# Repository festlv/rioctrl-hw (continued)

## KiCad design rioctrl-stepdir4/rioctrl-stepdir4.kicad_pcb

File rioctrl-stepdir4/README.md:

# rioctrl-stepdir4

This module provides 4 axis of step/dir/enable signals.
* Step/dir signals are differential 5V.
* Enable signal is at the same voltage as controller's DC input.

The connectors are RJ45 (intended use is either with motor-drive specific breakout board or a generic screw-terminal type breakout board).

RJ45 green LED is wired to enable signal.

## Pinout (when using breakouts/rioctrl-rj45-breakout):

| Pin | Signal |
|-----|--------|
| 1   | Step + |
| 2   | Step - |
| 3   | Dir -  |
| 4   | Enable |
| 5   | GND    |
| 6   | Dir -  |
| 7   | GND    |
| 8   | GND    |

# Changelog

## v1.1
* Fixed slot's pin-header position (was offset by 4 mm)
* Rename silkscreen labels from axis 1..4 to join 0..3 to match riocore/LinuxCNC convention
 
## v1.0
Initial released version.

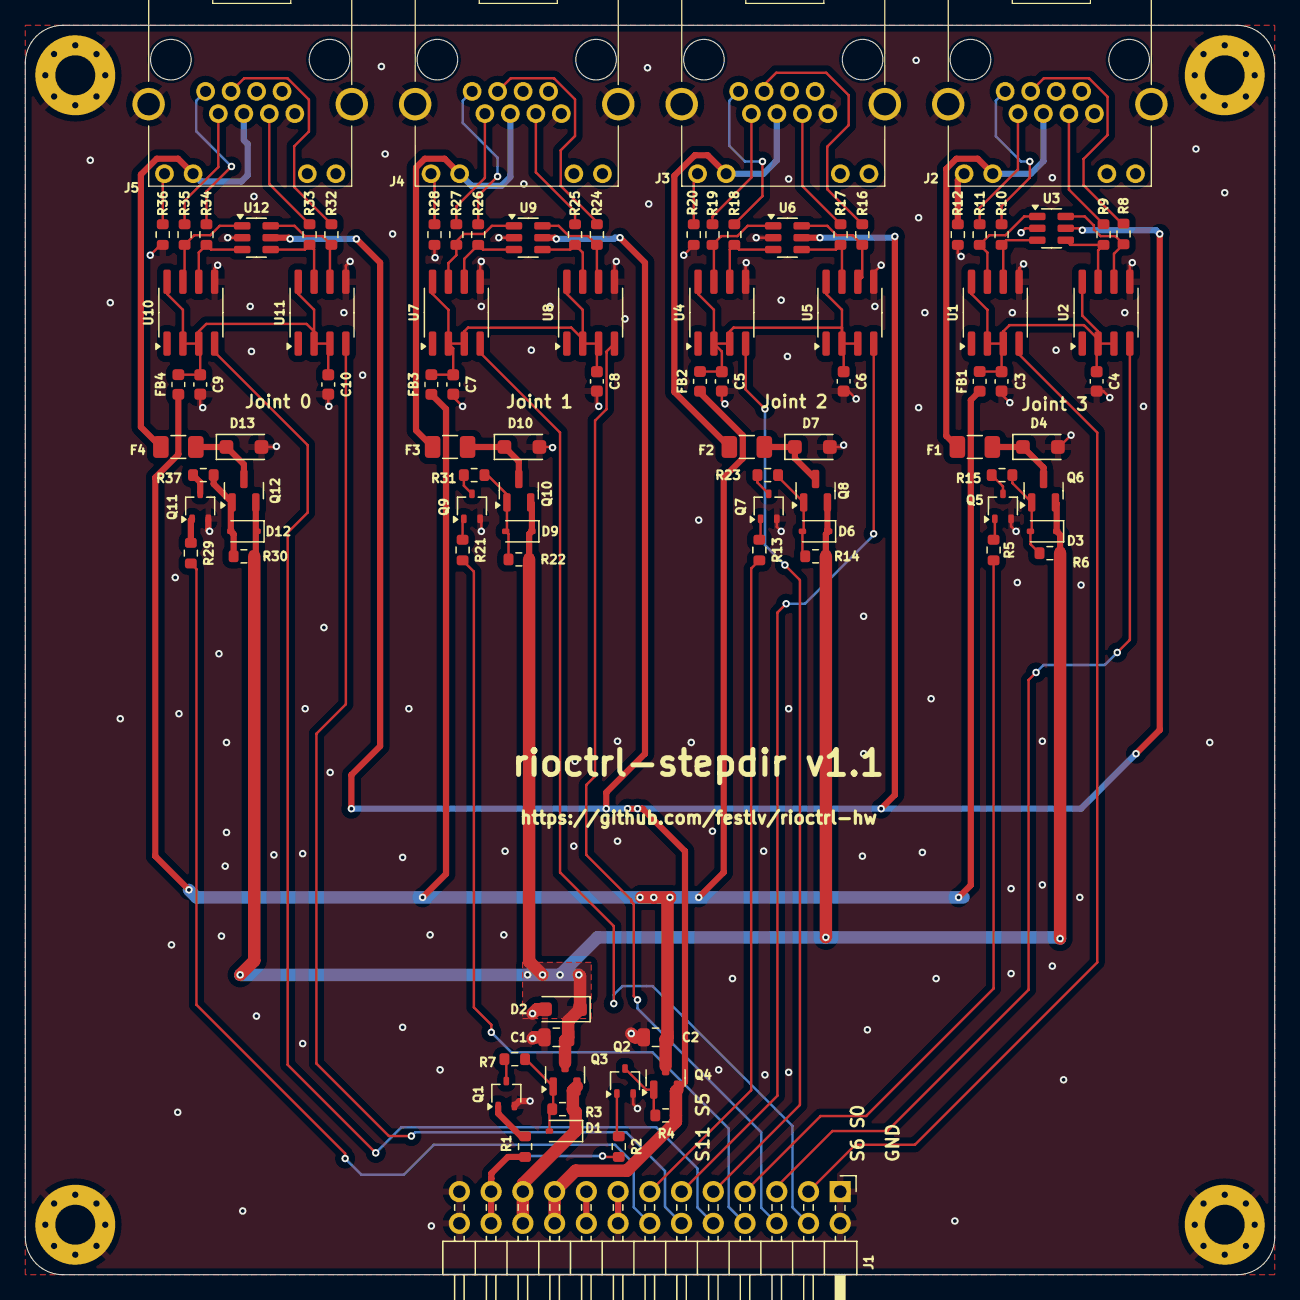
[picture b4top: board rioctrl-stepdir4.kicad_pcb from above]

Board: 2 copper layers, 100.0 x 100.0 mm, 98 parts (0 on the bottom side), 84 nets.

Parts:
C1, C2: 10uF; C_0805_2012Metric
C3, C4, C5, C6, C7, C8, C9, C10: 0.1uF; C_0603_1608Metric
D1, D3, D6, D9, D12: BZT52C10S; D_SOD-323
D2, D4, D7, D10, D13: SMF24A; D_SOD-123F
F1, F2, F3, F4: BSMD1206-100-24V; Fuse_1206_3216Metric
FB1, FB2, FB3, FB4: FB_100R_3A; L_0603_1608Metric
H1, H2, H3, H4: MH_3.2mm; MountingHole_3.2mm_M3_Pad_Via
J1: Conn_02x13_Odd_Even; PinHeader_2x13_P2.54mm_Horizontal
J2, J3, J4, J5: RJ45_LED_Shielded; R-RJ45R08P-C000
Q1, Q2, Q5, Q7, Q9, Q11: BSS138W; SOT-323_SC-70
Q3, Q4, Q6, Q8, Q10, Q12: AO3401A; SOT-23
R1, R2, R3, R4, R5, R6, R7, R12, R13, R14, R15, R20, R21, R22, R23, R28, R29, R30, R31, R36, R37: 10K; R_0603_1608Metric
R8, R9, R10, R11, R16, R17, R18, R19, R24, R25, R26, R27, R32, R33, R34, R35: 100R; R_0603_1608Metric
U1, U2, U4, U5, U7, U8, U10, U11: CS48505S; SOIC-8_3.9x4.9mm_P1.27mm
U3, U6, U9, U12: USBLC6-4SC6; SOT-23-6

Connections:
+3V3: J1.17, J1.18
+5V: J1.19, J1.20, Q4.2 (S), R4.1, U3.5 (VBUS), U6.5 (VBUS), U9.5 (VBUS), U12.5 (VBUS)
+5V_EN: C2.1, FB1.1, FB2.1, FB3.1, FB4.1, Q4.3 (D)
+24V: D1.1 (K), J1.21, J1.22, Q3.2 (S), R3.1
+24V_EN: C1.1, D2.1 (A1), D3.1 (K), D6.1 (K), D9.1 (K), D12.1 (K), Q3.3 (D), Q6.2 (S), Q8.2 (S), Q10.2 (S), Q12.2 (S), R6.1, R14.1, R22.1, R30.1
/Slot input/S0: J1.3, U1.4 (DI)
/Slot input/S1: J1.5, U2.4 (DI)
/Slot input/S2: J1.7, R5.2
/Slot input/S3: J1.9, U4.4 (DI)
/Slot input/S4: J1.11, U5.4 (DI)
/Slot input/S5: J1.13, R13.2
/Slot input/S6: J1.4, U7.4 (DI)
/Slot input/S7: J1.6, U8.4 (DI)
/Slot input/S8: J1.8, R21.2
/Slot input/S9: J1.10, U10.4 (DI)
/Slot input/S10: J1.12, U11.4 (DI)
/Slot input/S11: J1.14, R29.2
/Slot input/SlotEN: J1.23, J1.24, R1.2, R2.2
/Step dir output 1/DIR_OUT_N: R33.1, U11.7 (B), U12.4 (I/O3)
/Step dir output 1/DIR_OUT_P: R32.1, U11.6 (A), U12.6 (I/O4)
/Step dir output 1/DIR_OUT_P_N: J5.6, R33.2
/Step dir output 1/DIR_OUT_P_P: J5.3, R32.2
/Step dir output 1/EN_OUT: F4.2, J5.4, J5.10
/Step dir output 1/STEP_OUT_N: R35.1, U10.7 (B), U12.1 (I/O1)
/Step dir output 1/STEP_OUT_P: R34.1, U10.6 (A), U12.3 (I/O2)
/Step dir output 1/STEP_OUT_P_N: J5.2, R35.2
/Step dir output 1/STEP_OUT_P_P: J5.1, R34.2
/Step dir output 2/DIR_OUT_N: R25.1, U8.7 (B), U9.4 (I/O3)
/Step dir output 2/DIR_OUT_P: R24.1, U8.6 (A), U9.6 (I/O4)
/Step dir output 2/DIR_OUT_P_N: J4.6, R25.2
/Step dir output 2/DIR_OUT_P_P: J4.3, R24.2
/Step dir output 2/EN_OUT: F3.2, J4.4, J4.10
/Step dir output 2/STEP_OUT_N: R27.1, U7.7 (B), U9.1 (I/O1)
/Step dir output 2/STEP_OUT_P: R26.1, U7.6 (A), U9.3 (I/O2)
/Step dir output 2/STEP_OUT_P_N: J4.2, R27.2
/Step dir output 2/STEP_OUT_P_P: J4.1, R26.2
/Step dir output 3/DIR_OUT_N: R17.1, U5.7 (B), U6.4 (I/O3)
/Step dir output 3/DIR_OUT_P: R16.1, U5.6 (A), U6.6 (I/O4)
/Step dir output 3/DIR_OUT_P_N: J3.6, R17.2
/Step dir output 3/DIR_OUT_P_P: J3.3, R16.2
/Step dir output 3/EN_OUT: F2.2, J3.4, J3.10
/Step dir output 3/STEP_OUT_N: R19.1, U4.7 (B), U6.1 (I/O1)
/Step dir output 3/STEP_OUT_P: R18.1, U4.6 (A), U6.3 (I/O2)
/Step dir output 3/STEP_OUT_P_N: J3.2, R19.2
/Step dir output 3/STEP_OUT_P_P: J3.1, R18.2
/Step dir output 4/DIR_OUT_N: R9.1, U2.7 (B), U3.4 (I/O3)
/Step dir output 4/DIR_OUT_P: R8.1, U2.6 (A), U3.6 (I/O4)
/Step dir output 4/DIR_OUT_P_N: J2.6, R9.2
/Step dir output 4/DIR_OUT_P_P: J2.3, R8.2
/Step dir output 4/EN_OUT: F1.2, J2.4, J2.10
/Step dir output 4/STEP_OUT_N: R11.1, U1.7 (B), U3.1 (I/O1)
/Step dir output 4/STEP_OUT_P: R10.1, U1.6 (A), U3.3 (I/O2)
/Step dir output 4/STEP_OUT_P_N: J2.2, R11.2
/Step dir output 4/STEP_OUT_P_P: J2.1, R10.2
GND: C1.2, C2.2, C3.2, C4.2, C5.2, C6.2, C7.2, C8.2, C9.2, C10.2, D2.2 (A2), D4.2 (A2), D7.2 (A2), D10.2 (A2), D13.2 (A2), H1.1, H2.1, H3.1, H4.1, J1.1, J1.2, J1.15, J1.16, J1.25, J1.26, J2.5, J2.7, J2.8, J2.SH, J3.5, J3.7, J3.8, J3.SH, J4.5, J4.7, J4.8, J4.SH, J5.5, J5.7, J5.8, J5.SH, Q1.2 (S), Q2.2 (S), Q5.2 (S), Q7.2 (S), Q9.2 (S), Q11.2 (S), R12.2, R20.2, R28.2, R36.2, U1.5 (GND), U2.5 (GND), U3.2 (GND), U4.5 (GND), U5.5 (GND), U6.2 (GND), U7.5 (GND), U8.5 (GND), U9.2 (GND), U10.5 (GND), U11.5 (GND), U12.2 (GND)
unnamed: D1.2 (A), Q3.1 (G), R3.2, R7.1
unnamed: D3.2 (A), Q6.1 (G), R6.2, R15.1
unnamed: D4.1 (A1), F1.1, Q6.3 (D)
unnamed: D6.2 (A), Q8.1 (G), R14.2, R23.1
unnamed: D7.1 (A1), F2.1, Q8.3 (D)
unnamed: D9.2 (A), Q10.1 (G), R22.2, R31.1
unnamed: D10.1 (A1), F3.1, Q10.3 (D)
unnamed: D12.2 (A), Q12.1 (G), R30.2, R37.1
unnamed: D13.1 (A1), F4.1, Q12.3 (D)
unnamed: J2.9, R12.1
unnamed: J3.9, R20.1
unnamed: J4.9, R28.1
unnamed: J5.9, R36.1
unnamed: Q1.3 (D), R7.2
unnamed: Q1.1 (G), R1.1
unnamed: Q2.3 (D), Q4.1 (G), R4.2
unnamed: Q2.1 (G), R2.1
unnamed: Q5.3 (D), R15.2
unnamed: Q5.1 (G), R5.1
unnamed: Q7.3 (D), R23.2
unnamed: Q7.1 (G), R13.1
unnamed: Q9.3 (D), R31.2
unnamed: Q9.1 (G), R21.1
unnamed: Q11.3 (D), R37.2
unnamed: Q11.1 (G), R29.1
unnamed: C3.1, C4.1, FB1.2, U1.2 (~RE), U1.3 (DE), U1.8 (VCC), U2.2 (~RE), U2.3 (DE), U2.8 (VCC)
unnamed: C5.1, C6.1, FB2.2, U4.2 (~RE), U4.3 (DE), U4.8 (VCC), U5.2 (~RE), U5.3 (DE), U5.8 (VCC)
unnamed: C7.1, C8.1, FB3.2, U7.2 (~RE), U7.3 (DE), U7.8 (VCC), U8.2 (~RE), U8.3 (DE), U8.8 (VCC)
unnamed: C9.1, C10.1, FB4.2, U10.2 (~RE), U10.3 (DE), U10.8 (VCC), U11.2 (~RE), U11.3 (DE), U11.8 (VCC)

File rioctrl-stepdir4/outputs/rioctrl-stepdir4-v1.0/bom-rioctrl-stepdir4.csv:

"Refs","Value","Footprint","Manufacturer","MPN","Qty","DNP","LCSC#"
"C1,C2","10uF","Capacitor_SMD:C_0805_2012Metric","","GRM21BR61H106KE43L","2","","C440198"
"C3-C10","0.1uF","Capacitor_SMD:C_0603_1608Metric","","","8","","C14663"
"D1,D3,D6,D9,D12","BZT52C10S","Diode_SMD:D_SOD-323","YFW","BZT52C10S","5","","C5270769"
"D2,D4,D7,D10,D13","SMF24A","Diode_SMD:D_SOD-123F","Shandong Jingdao Microelectronics","SMF24A","5","","C169430"
"F1-F4","BSMD1206-100-24V","Fuse:Fuse_1206_3216Metric","BHFUSE","BSMD1206-100-24V","4","","C910830"
"FB1-FB4","FB_100R_3A","Inductor_SMD:L_0603_1608Metric","Sunlord","UPZ1608E101-3R0TF","4","","C96995"
"J1","Conn_02x13_Odd_Even","Connector_PinHeader_2.54mm:PinHeader_2x13_P2.54mm_Horizontal","","","1","","C2894993"
"J2-J5","RJ45_LED_Shielded","hadv-connectors:R-RJ45R08P-C000","Ckmtw(Shenzhen Cankemeng)","R-RJ45R08P-C000","4","","C386757"
"Q1,Q2,Q5,Q7,Q9,Q11","BSS138W","Package_TO_SOT_SMD:SOT-323_SC-70","Jiangsu Changjing Electronics Technology Co., Ltd.","BSS138W","6","","C504052"
"Q3,Q4,Q6,Q8,Q10,Q12","AO3401A","Package_TO_SOT_SMD:SOT-23","UMW","AO3401A","6","","C347476"
"R1-R7,R12-R15,R20-R23,R28-R31,R36,R37","10K","Resistor_SMD:R_0603_1608Metric","","","21","","C98220"
"R8-R11,R16-R19,R24-R27,R32-R35","100R","Resistor_SMD:R_0603_1608Metric","","","16","","C105588"
"U1,U2,U4,U5,U7,U8,U10,U11","CS48505S","Package_SO:SOIC-8_3.9x4.9mm_P1.27mm","Chipanalog","CS48505S","8","","C3202824"
"U3,U6,U9,U12","USBLC6-4SC6","Package_TO_SOT_SMD:SOT-23-6","TECH PUBLIC","USBLC6-4SC6","4","","C5197386"

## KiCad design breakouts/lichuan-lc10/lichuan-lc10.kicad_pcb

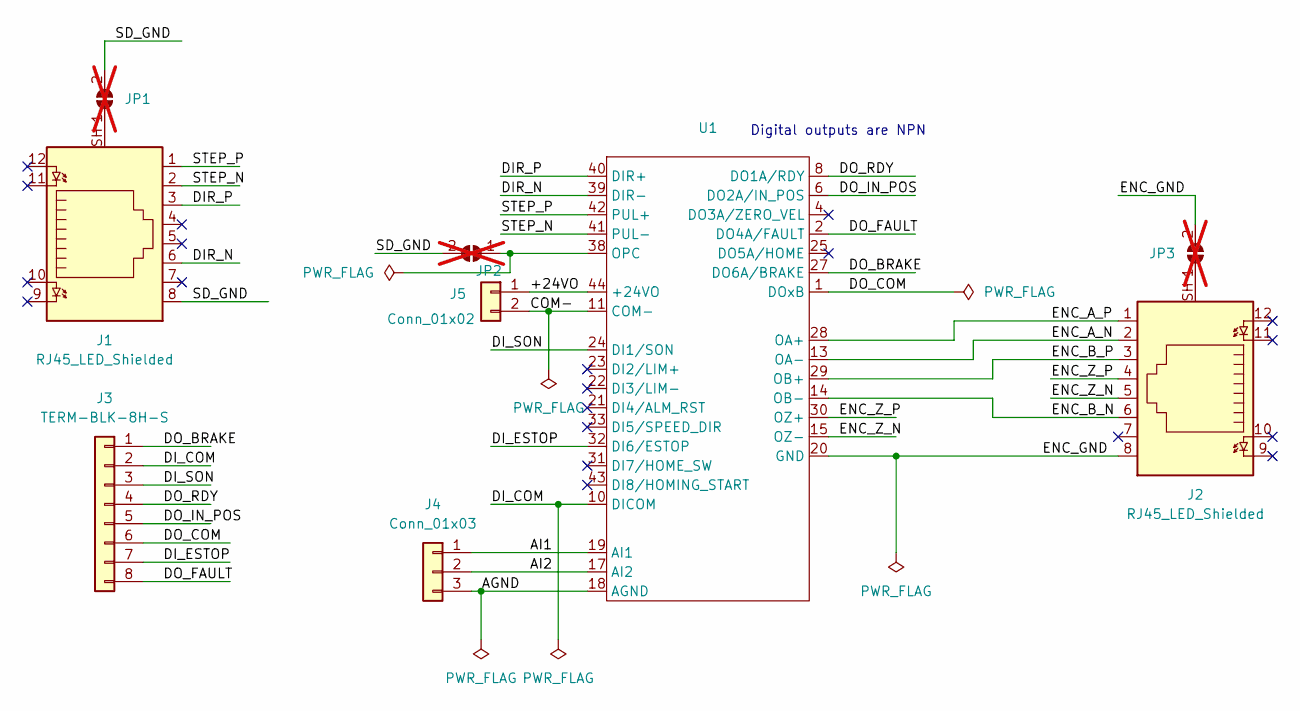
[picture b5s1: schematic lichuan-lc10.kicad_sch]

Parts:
J1, J2: RJ45_LED_Shielded; R-RJ45R08P-C000; MPN R-RJ45R08P-C000; LCSC# C386757
J3: TERM-BLK-8H-S; MX250-3.5-08P-B; MPN MX250-3.5-08P-B-GY01-Cu-A; LCSC# C7470122
J4: Conn_01x03; PinHeader_1x03_P2.54mm_Vertical
J5: Conn_01x02; PinHeader_1x02_P2.54mm_Vertical
JP1, JP2, JP3: SolderJumper_2_Open; SolderJumper-2_P1.3mm_Open_RoundedPad1.0x1.5mm; not fitted
U1: DSUB-44-HD_Male_Horizontal_P2.29x1.98mm_EdgePinOffset8.35mm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; MPN DS1038-44MBNSIA74-0CC; LCSC# C77845

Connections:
/+24VO: J5.1, U1.44 (+24VO)
/AGND: J4.3, U1.16 (AGND), U1.18 (AGND)
/AI1: J4.1, U1.19 (AI1)
/AI2: J4.2, U1.17 (AI2)
/COM-: J5.2, U1.11 (COM-), U1.12 (COM-)
/DIR_N: J1.6, U1.39 (DIR-)
/DIR_P: J1.3, U1.40 (DIR+)
/DI_COM: J3.2, U1.10 (DICOM)
/DI_ESTOP: J3.7, U1.32 (DI6/ESTOP)
/DI_SON: J3.3, U1.24 (DI1/SON)
/DO_BRAKE: J3.1, U1.27 (DO6A/BRAKE)
/DO_COM: J3.6, U1.1 (DOxB), U1.3 (DO3B), U1.5 (DO2B), U1.7 (DO1B), U1.9 (DO5B), U1.26 (DO6B)
/DO_FAULT: J3.8, U1.2 (DO4A/FAULT)
/DO_IN_POS: J3.5, U1.6 (DO2A/IN_POS)
/DO_RDY: J3.4, U1.8 (DO1A/RDY)
/ENC_A_N: J2.2, U1.13 (OA-)
/ENC_A_P: J2.1, U1.28 (OA+)
/ENC_B_N: J2.6, U1.14 (OB-)
/ENC_B_P: J2.3, U1.29 (OB+)
/ENC_GND: J2.8, JP3.2 (B), U1.20 (GND)
/ENC_Z_N: J2.5, U1.15 (OZ-)
/ENC_Z_P: J2.4, U1.30 (OZ+)
/SD_GND: J1.8, JP1.2 (B), JP2.2 (B)
/STEP_N: J1.2, U1.41 (PUL-)
/STEP_P: J1.1, U1.42 (PUL+)
unnamed: J1.SH, JP1.1 (A)
unnamed: JP2.1 (A), U1.38 (OPC)
unnamed: J2.SH, JP3.1 (A)

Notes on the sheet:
Digital outputs are NPN

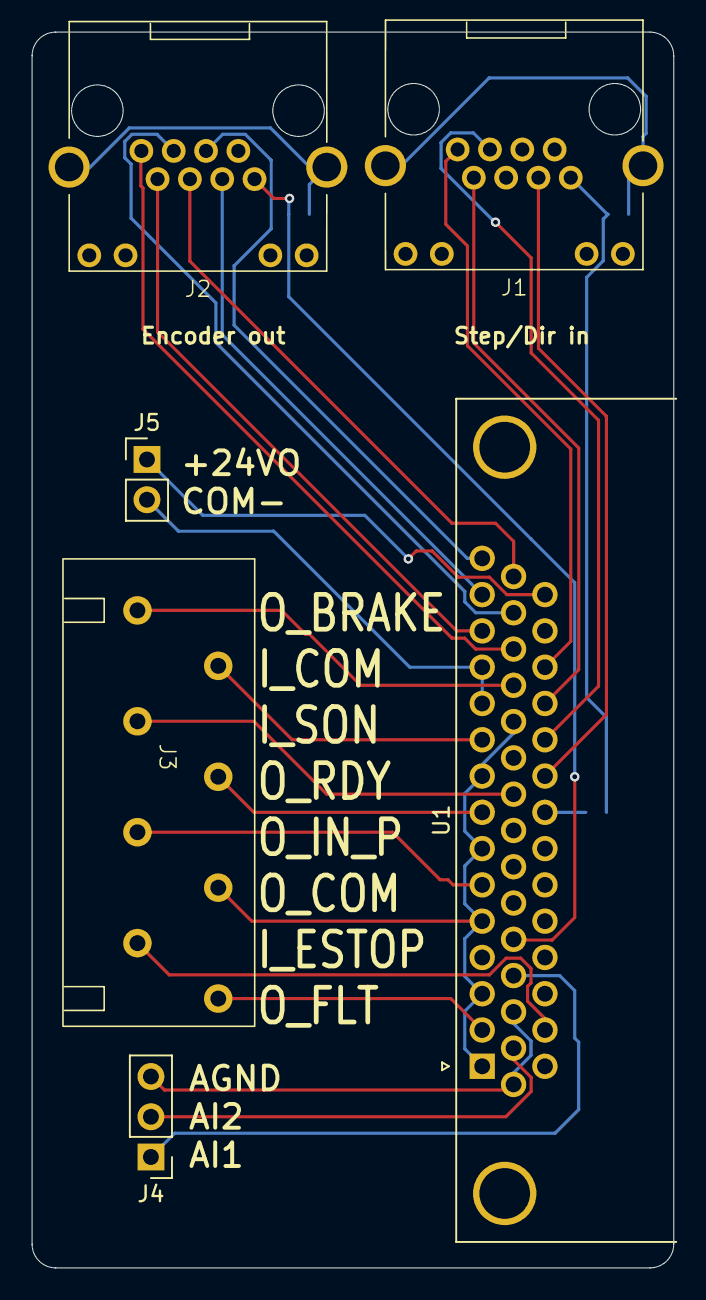
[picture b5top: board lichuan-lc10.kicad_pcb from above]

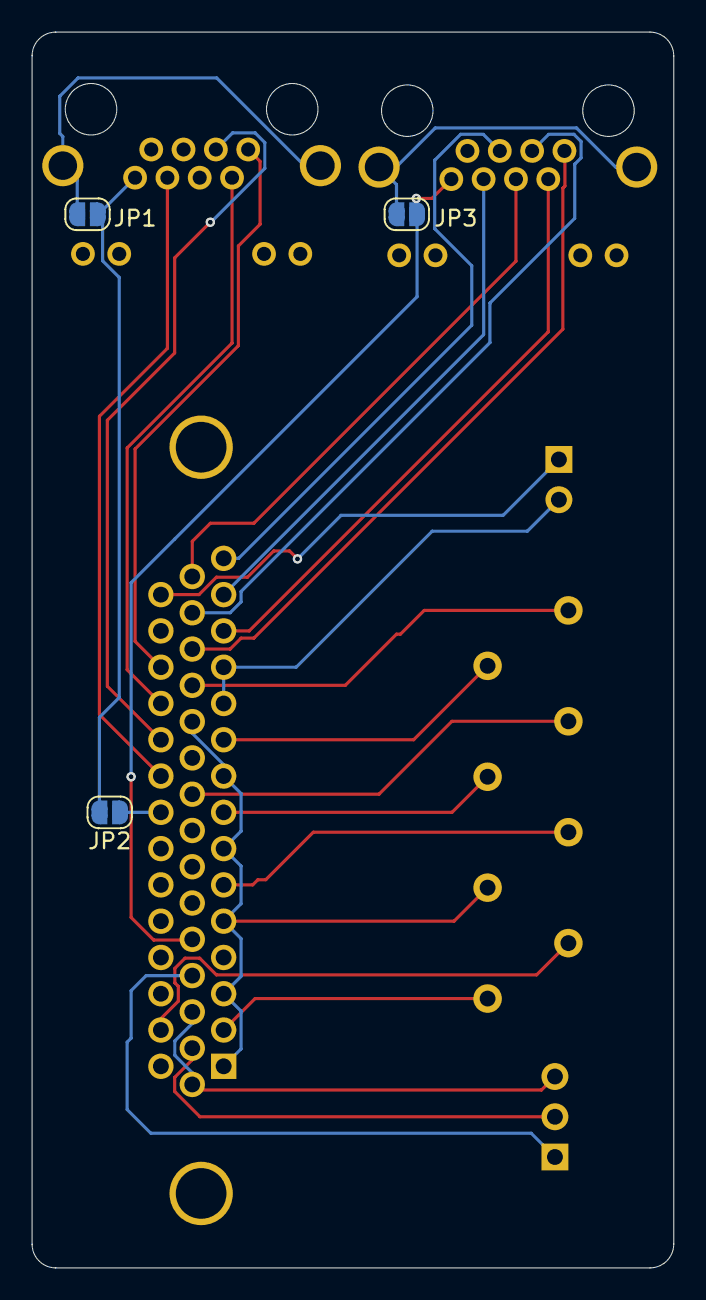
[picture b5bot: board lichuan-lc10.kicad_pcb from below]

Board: 2 copper layers, 40.5 x 78.0 mm, 9 parts (3 on the bottom side), 28 nets.

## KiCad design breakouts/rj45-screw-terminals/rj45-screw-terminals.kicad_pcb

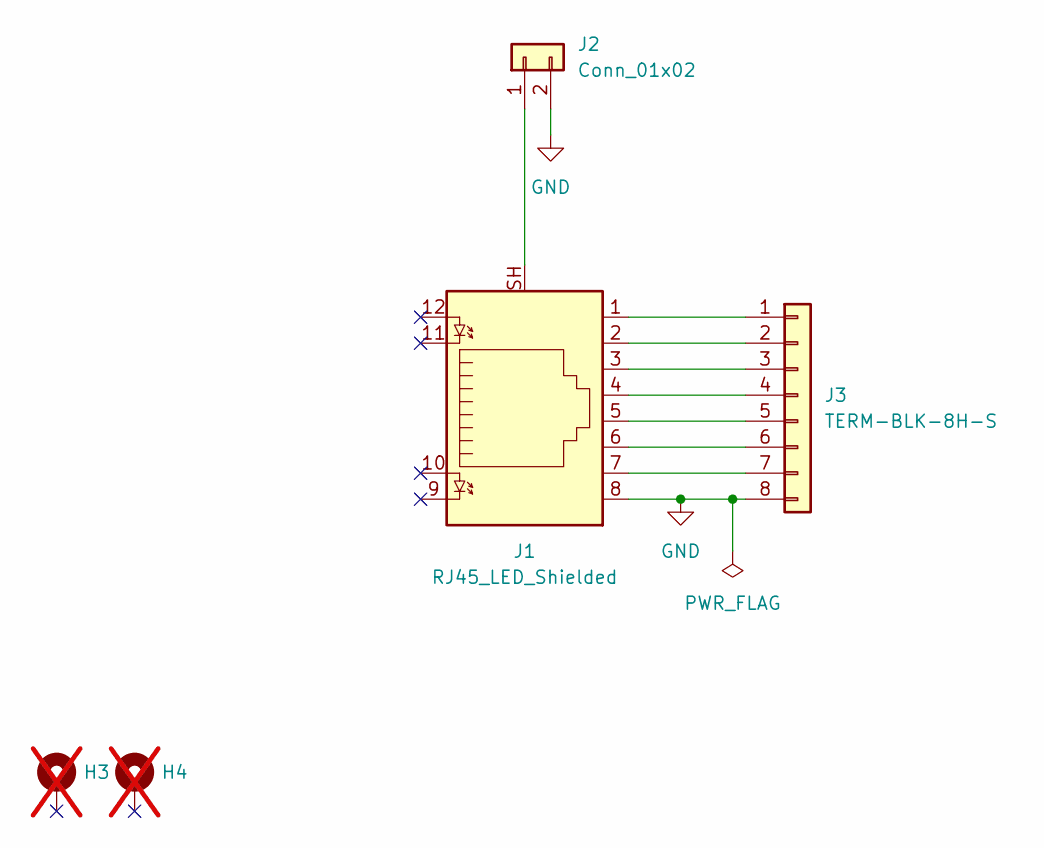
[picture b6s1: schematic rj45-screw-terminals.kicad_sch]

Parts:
H3, H4: MH_3.2mm; MountingHole_3.2mm_M3_Pad_Via; not fitted
J1: RJ45_LED_Shielded; R-RJ45R08P-C000; MPN R-RJ45R08P-C000; LCSC# C386757
J2: Conn_01x02; PinHeader_1x02_P2.54mm_Vertical
J3: TERM-BLK-8H-S; MX250-3.5-08P-B; MPN MX250-3.5-08P-B-GY01-Cu-A; LCSC# C7470122

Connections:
GND: J1.8, J2.2, J3.8
unnamed: J1.SH, J2.1
unnamed: J1.1, J3.1
unnamed: J1.2, J3.2
unnamed: J1.3, J3.3
unnamed: J1.4, J3.4
unnamed: J1.5, J3.5
unnamed: J1.6, J3.6
unnamed: J1.7, J3.7

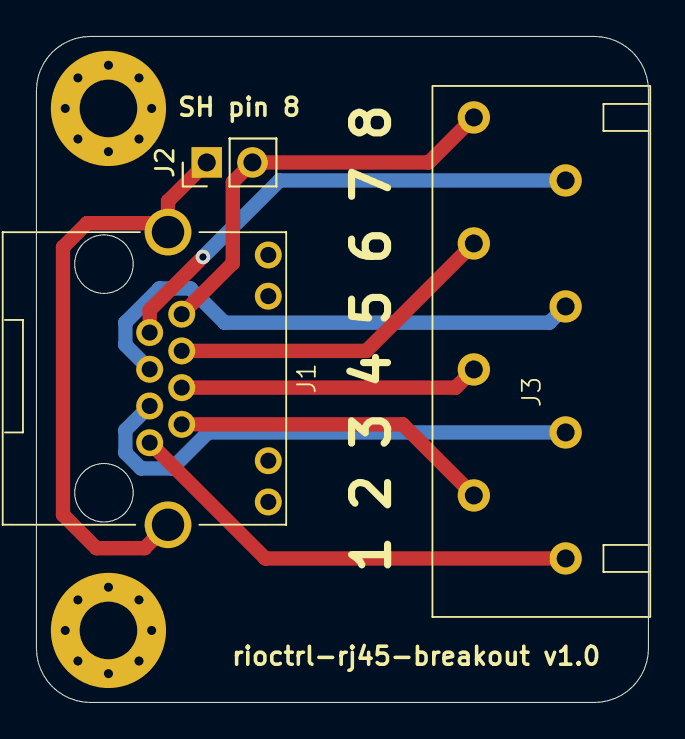
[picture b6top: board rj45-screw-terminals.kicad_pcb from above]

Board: 2 copper layers, 34.0 x 37.0 mm, 5 parts (0 on the bottom side), 9 nets.

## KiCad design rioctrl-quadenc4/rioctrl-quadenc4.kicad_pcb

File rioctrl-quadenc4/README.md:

# rioctrl-quadenc4

This module provides 4 axis of differential quadrature encoder inputs, intended for 5V differential output encoders.
Each axis has A, B and Z inputs.

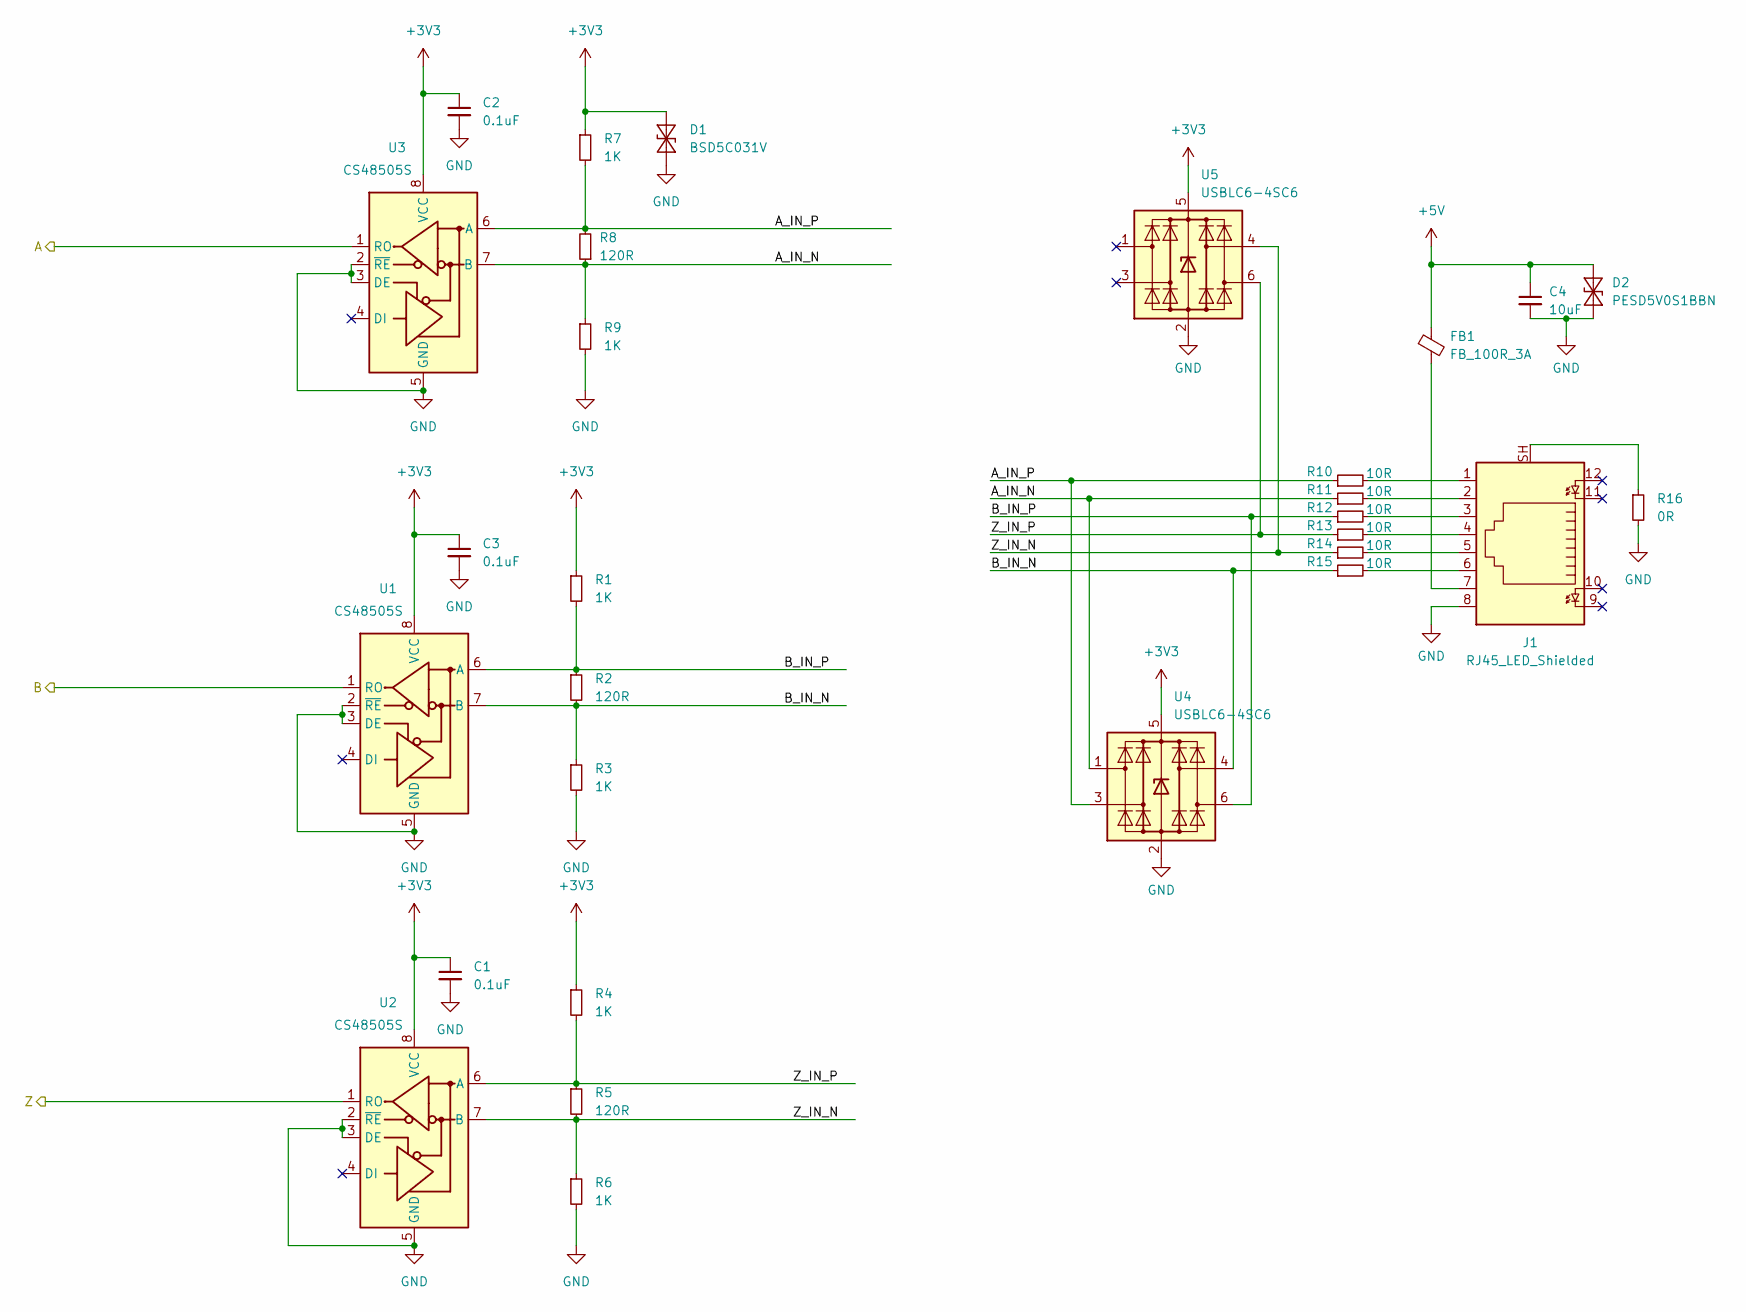
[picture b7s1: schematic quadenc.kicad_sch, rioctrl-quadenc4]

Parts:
C1, C2, C3: 0.1uF; C_0603_1608Metric; LCSC# C14663
C4: 10uF; C_0805_2012Metric; MPN GRM21BR61H106KE43L; LCSC# C440198
D1: BSD5C031V; D_SOD-523; MPN BSD5C031V; LCSC# C151984
D2: PESD5V0S1BBN; D_SOD-523; MPN PESD5V0S1BBN; LCSC# C314264
FB1: FB_100R_3A; L_0603_1608Metric; MPN UPZ1608E101-3R0TF; LCSC# C96995
J1: RJ45_LED_Shielded; R-RJ45R08P-C000; MPN R-RJ45R08P-C000; LCSC# C386757
R1, R3, R4, R6, R7, R9: 1K; R_0603_1608Metric; LCSC# C22548
R2, R5, R8: 120R; R_0603_1608Metric; LCSC# C114640
R10, R11, R12, R13, R14, R15: 10R; R_0603_1608Metric; LCSC# C109318
R16: 0R; R_0603_1608Metric; LCSC# C95177
U1, U2, U3: CS48505S; SOIC-8_3.9x4.9mm_P1.27mm; MPN CS48505S; LCSC# C3202824
U4, U5: USBLC6-4SC6; SOT-23-6; MPN USBLC6-4SC6; LCSC# C5197386

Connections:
+3V3: C1.1, C2.1, C3.1, D1.1 (A1), R1.1, R4.1, R7.1, U1.8 (VCC), U2.8 (VCC), U3.8 (VCC), U4.5 (VBUS), U5.5 (VBUS); also elsewhere on the board
+5V: C4.1, D2.2 (A2), FB1.1; also elsewhere on the board
/Quadenc/A: U3.1 (RO); also elsewhere on the board
/Quadenc/A_IN_N: R8.1, R9.1, R11.1, U3.7 (B), U4.1 (I/O1)
/Quadenc/A_IN_P: R7.2, R8.2, R10.1, U3.6 (A), U4.3 (I/O2)
/Quadenc/B: U1.1 (RO); also elsewhere on the board
/Quadenc/B_IN_N: R2.2, R3.1, R15.1, U1.7 (B), U4.4 (I/O3)
/Quadenc/B_IN_P: R1.2, R2.1, R12.1, U1.6 (A), U4.6 (I/O4)
/Quadenc/Z: U2.1 (RO); also elsewhere on the board
/Quadenc/Z_IN_N: R5.2, R6.1, R14.1, U2.7 (B), U5.4 (I/O3)
/Quadenc/Z_IN_P: R4.2, R5.1, R13.1, U2.6 (A), U5.6 (I/O4)
GND: C1.2, C2.2, C3.2, C4.2, D1.2 (A2), D2.1 (A1), J1.8, R3.2, R6.2, R9.2, R16.2, U1.2 (~RE), U1.3 (DE), U1.5 (GND), U2.2 (~RE), U2.3 (DE), U2.5 (GND), U3.2 (~RE), U3.3 (DE), U3.5 (GND), U4.2 (GND), U5.2 (GND); also elsewhere on the board
unnamed: FB1.2, J1.7
unnamed: J1.1, R10.2
unnamed: J1.2, R11.2
unnamed: J1.3, R12.2
unnamed: J1.4, R13.2
unnamed: J1.5, R14.2
unnamed: J1.6, R15.2
unnamed: J1.SH, R16.1

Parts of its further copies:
C5, C6, C7, C9, C10, C11, C13, C14, C15: 0.1uF; C_0603_1608Metric; LCSC# C14663
C8, C12, C16: 10uF; C_0805_2012Metric; MPN GRM21BR61H106KE43L; LCSC# C440198
D3, D5, D7: BSD5C031V; D_SOD-523; MPN BSD5C031V; LCSC# C151984
D4, D6, D8: PESD5V0S1BBN; D_SOD-523; MPN PESD5V0S1BBN; LCSC# C314264
FB2, FB3, FB4: FB_100R_3A; L_0603_1608Metric; MPN UPZ1608E101-3R0TF; LCSC# C96995
J3, J4, J5: RJ45_LED_Shielded; R-RJ45R08P-C000; MPN R-RJ45R08P-C000; LCSC# C386757
R17, R19, R20, R22, R23, R25, R33, R35, R36, R38, R39, R41, R49, R51, R52, R54, R55, R57: 1K; R_0603_1608Metric; LCSC# C22548
R18, R21, R24, R34, R37, R40, R50, R53, R56: 120R; R_0603_1608Metric; LCSC# C114640
R26, R27, R28, R29, R30, R31, R42, R43, R44, R45, R46, R47, R58, R59, R60, R61, R62, R63: 10R; R_0603_1608Metric; LCSC# C109318
R32, R48, R64: 0R; R_0603_1608Metric; LCSC# C95177
U6, U7, U8, U11, U12, U13, U16, U17, U18: CS48505S; SOIC-8_3.9x4.9mm_P1.27mm; MPN CS48505S; LCSC# C3202824
U9, U10, U14, U15, U19, U20: USBLC6-4SC6; SOT-23-6; MPN USBLC6-4SC6; LCSC# C5197386

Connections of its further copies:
+3V3: C5.1, C6.1, C7.1, C9.1, C10.1, C11.1, C13.1, C14.1, C15.1, D3.1 (A1), D5.1 (A1), D7.1 (A1), R17.1, R20.1, R23.1, R33.1, R36.1, R39.1, R49.1, R52.1, R55.1, U6.8 (VCC), U7.8 (VCC), U8.8 (VCC), U9.5 (VBUS), U10.5 (VBUS), U11.8 (VCC), U12.8 (VCC), U13.8 (VCC), U14.5 (VBUS), U15.5 (VBUS), U16.8 (VCC), U17.8 (VCC), U18.8 (VCC), U19.5 (VBUS), U20.5 (VBUS); also elsewhere on the board
+5V: C8.1, C12.1, C16.1, D4.2 (A2), D6.2 (A2), D8.2 (A2), FB2.1, FB3.1, FB4.1; also elsewhere on the board
/Quadenc1/A: U8.1 (RO); also elsewhere on the board
/Quadenc1/A_IN_N: R24.1, R25.1, R27.1, U8.7 (B), U9.1 (I/O1)
/Quadenc1/A_IN_P: R23.2, R24.2, R26.1, U8.6 (A), U9.3 (I/O2)
/Quadenc1/B: U6.1 (RO); also elsewhere on the board
/Quadenc1/B_IN_N: R18.2, R19.1, R31.1, U6.7 (B), U9.4 (I/O3)
/Quadenc1/B_IN_P: R17.2, R18.1, R28.1, U6.6 (A), U9.6 (I/O4)
/Quadenc1/Z: U7.1 (RO); also elsewhere on the board
/Quadenc1/Z_IN_N: R21.2, R22.1, R30.1, U7.7 (B), U10.4 (I/O3)
/Quadenc1/Z_IN_P: R20.2, R21.1, R29.1, U7.6 (A), U10.6 (I/O4)
/Quadenc2/A: U13.1 (RO); also elsewhere on the board
/Quadenc2/A_IN_N: R40.1, R41.1, R43.1, U13.7 (B), U14.1 (I/O1)
/Quadenc2/A_IN_P: R39.2, R40.2, R42.1, U13.6 (A), U14.3 (I/O2)
/Quadenc2/B: U11.1 (RO); also elsewhere on the board
/Quadenc2/B_IN_N: R34.2, R35.1, R47.1, U11.7 (B), U14.4 (I/O3)
/Quadenc2/B_IN_P: R33.2, R34.1, R44.1, U11.6 (A), U14.6 (I/O4)
/Quadenc2/Z: U12.1 (RO); also elsewhere on the board
/Quadenc2/Z_IN_N: R37.2, R38.1, R46.1, U12.7 (B), U15.4 (I/O3)
/Quadenc2/Z_IN_P: R36.2, R37.1, R45.1, U12.6 (A), U15.6 (I/O4)
/Quadenc3/A: U18.1 (RO); also elsewhere on the board
/Quadenc3/A_IN_N: R56.1, R57.1, R59.1, U18.7 (B), U19.1 (I/O1)
/Quadenc3/A_IN_P: R55.2, R56.2, R58.1, U18.6 (A), U19.3 (I/O2)
/Quadenc3/B: U16.1 (RO); also elsewhere on the board
/Quadenc3/B_IN_N: R50.2, R51.1, R63.1, U16.7 (B), U19.4 (I/O3)
/Quadenc3/B_IN_P: R49.2, R50.1, R60.1, U16.6 (A), U19.6 (I/O4)
/Quadenc3/Z: U17.1 (RO); also elsewhere on the board
/Quadenc3/Z_IN_N: R53.2, R54.1, R62.1, U17.7 (B), U20.4 (I/O3)
/Quadenc3/Z_IN_P: R52.2, R53.1, R61.1, U17.6 (A), U20.6 (I/O4)
GND: C5.2, C6.2, C7.2, C8.2, C9.2, C10.2, C11.2, C12.2, C13.2, C14.2, C15.2, C16.2, D3.2 (A2), D4.1 (A1), D5.2 (A2), D6.1 (A1), D7.2 (A2), D8.1 (A1), J3.8, J4.8, J5.8, R19.2, R22.2, R25.2, R32.2, R35.2, R38.2, R41.2, R48.2, R51.2, R54.2, R57.2, R64.2, U6.2 (~RE), U6.3 (DE), U6.5 (GND), U7.2 (~RE), U7.3 (DE), U7.5 (GND), U8.2 (~RE), U8.3 (DE), U8.5 (GND), U9.2 (GND), U10.2 (GND), U11.2 (~RE), U11.3 (DE), U11.5 (GND), U12.2 (~RE), U12.3 (DE), U12.5 (GND), U13.2 (~RE), U13.3 (DE), U13.5 (GND), U14.2 (GND), U15.2 (GND), U16.2 (~RE), U16.3 (DE), U16.5 (GND), U17.2 (~RE), U17.3 (DE), U17.5 (GND), U18.2 (~RE), U18.3 (DE), U18.5 (GND), U19.2 (GND), U20.2 (GND); also elsewhere on the board
unnamed: FB2.2, J3.7
unnamed: FB3.2, J4.7
unnamed: FB4.2, J5.7
unnamed: J3.1, R26.2
unnamed: J3.2, R27.2
unnamed: J3.3, R28.2
unnamed: J3.4, R29.2
unnamed: J3.5, R30.2
unnamed: J3.6, R31.2
unnamed: J3.SH, R32.1
unnamed: J4.1, R42.2
unnamed: J4.2, R43.2
unnamed: J4.3, R44.2
unnamed: J4.4, R45.2
unnamed: J4.5, R46.2
unnamed: J4.6, R47.2
unnamed: J4.SH, R48.1
unnamed: J5.1, R58.2
unnamed: J5.2, R59.2
unnamed: J5.3, R60.2
unnamed: J5.4, R61.2
unnamed: J5.5, R62.2
unnamed: J5.6, R63.2
unnamed: J5.SH, R64.1

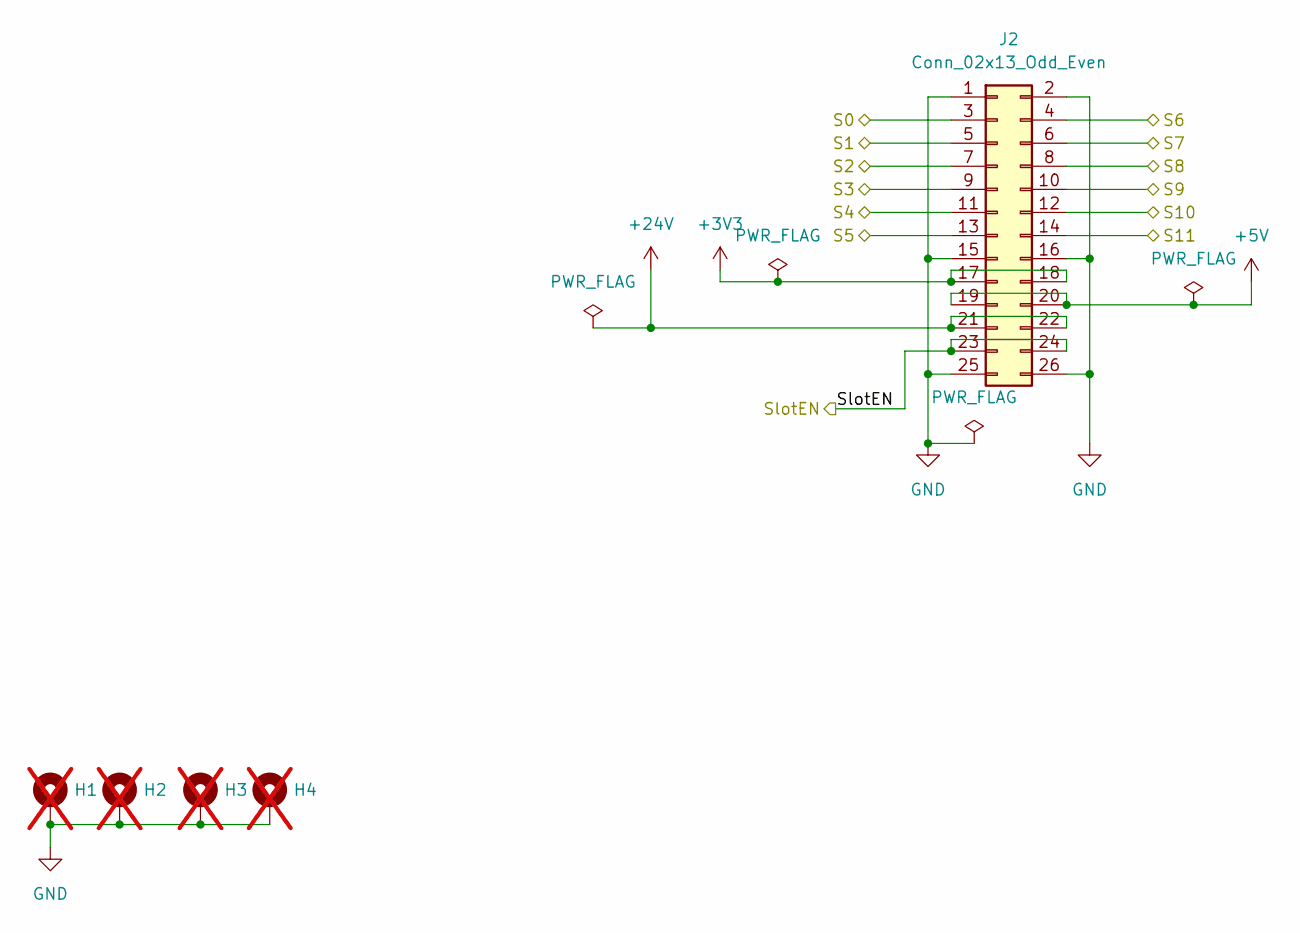
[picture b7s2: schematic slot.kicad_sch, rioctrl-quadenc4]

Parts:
H1, H2, H3, H4: MH_3.2mm; MountingHole_3.2mm_M3_Pad_Via; not fitted
J2: Conn_02x13_Odd_Even; PinHeader_2x13_P2.54mm_Horizontal; LCSC# C2894993

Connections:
+3V3: J2.17, J2.18; also elsewhere on the board
+5V: J2.19, J2.20; also elsewhere on the board
+24V: J2.21, J2.22
/Quadenc1/A: J2.13; also elsewhere on the board
/Quadenc1/B: J2.11; also elsewhere on the board
/Quadenc1/Z: J2.9; also elsewhere on the board
/Quadenc2/A: J2.8; also elsewhere on the board
/Quadenc2/B: J2.6; also elsewhere on the board
/Quadenc2/Z: J2.4; also elsewhere on the board
/Quadenc3/A: J2.14; also elsewhere on the board
/Quadenc3/B: J2.12; also elsewhere on the board
/Quadenc3/Z: J2.10; also elsewhere on the board
/Quadenc/A: J2.7; also elsewhere on the board
/Quadenc/B: J2.5; also elsewhere on the board
/Quadenc/Z: J2.3; also elsewhere on the board
/Slot/SlotEN: J2.23, J2.24
GND: H1.1, H2.1, H3.1, H4.1, J2.1, J2.2, J2.15, J2.16, J2.25, J2.26; also elsewhere on the board

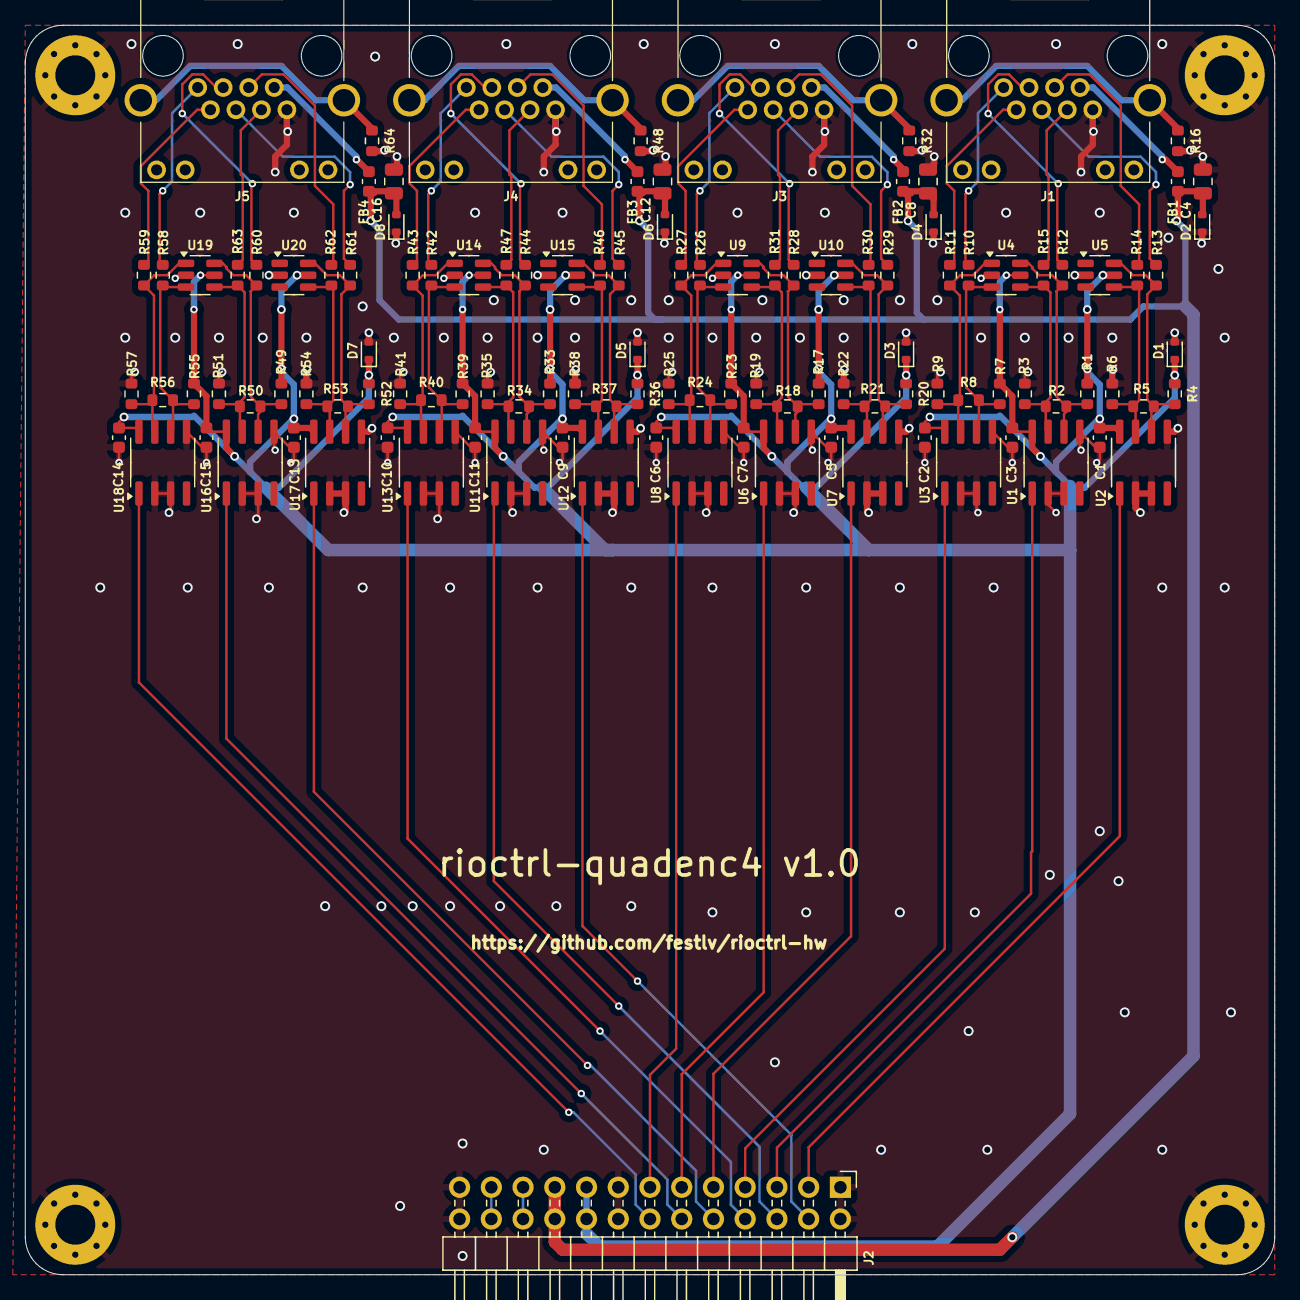
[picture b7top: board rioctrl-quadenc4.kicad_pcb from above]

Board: 2 copper layers, 100.0 x 100.0 mm, 121 parts (0 on the bottom side), 73 nets.

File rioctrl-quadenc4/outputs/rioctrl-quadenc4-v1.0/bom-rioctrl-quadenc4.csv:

"Refs","Value","Footprint","Manufacturer","MPN","Qty","DNP","LCSC#"
"C1-C3,C5-C7,C9-C11,C13-C15","0.1uF","Capacitor_SMD:C_0603_1608Metric","","","12","","C14663"
"C4,C8,C12,C16","10uF","Capacitor_SMD:C_0805_2012Metric","","GRM21BR61H106KE43L","4","","C440198"
"D1,D3,D5,D7","BSD5C031V","Diode_SMD:D_SOD-523","BORN","BSD5C031V","4","","C151984"
"D2,D4,D6,D8","PESD5V0S1BBN","Diode_SMD:D_SOD-523","BORN","PESD5V0S1BBN","4","","C314264"
"FB1-FB4","FB_100R_3A","Inductor_SMD:L_0603_1608Metric","Sunlord","UPZ1608E101-3R0TF","4","","C96995"
"J1,J3-J5","RJ45_LED_Shielded","hadv-connectors:R-RJ45R08P-C000","Ckmtw(Shenzhen Cankemeng)","R-RJ45R08P-C000","4","","C386757"
"J2","Conn_02x13_Odd_Even","Connector_PinHeader_2.54mm:PinHeader_2x13_P2.54mm_Horizontal","","","1","","C2894993"
"R1,R3,R4,R6,R7,R9,R17,R19,R20,R22,R23,R25,R33,R35,R36,R38,R39,R41,R49,R51,R52,R54,R55,R57","1K","Resistor_SMD:R_0603_1608Metric","","","24","","C22548"
"R2,R5,R8,R18,R21,R24,R34,R37,R40,R50,R53,R56","120R","Resistor_SMD:R_0603_1608Metric","","","12","","C114640"
"R10-R15,R26-R31,R42-R47,R58-R63","10R","Resistor_SMD:R_0603_1608Metric","","","24","","C109318"
"R16,R32,R48,R64","0R","Resistor_SMD:R_0603_1608Metric","","","4","","C95177"
"U1-U3,U6-U8,U11-U13,U16-U18","CS48505S","Package_SO:SOIC-8_3.9x4.9mm_P1.27mm","Chipanalog","CS48505S","12","","C3202824"
"U4,U5,U9,U10,U14,U15,U19,U20","USBLC6-4SC6","Package_TO_SOT_SMD:SOT-23-6","TECH PUBLIC","USBLC6-4SC6","8","","C5197386"
